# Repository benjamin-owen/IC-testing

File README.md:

# IC-testing
This repository contains a collection of ICs that I have tested.  Each folder from the root directory contains project files for the respective IC.  The file/folder structure follows my kicad-project-template template.

## Important version control information
This project uses submodules to keep libraries up-to-date.  The following commands must be used when cloning or to update the submodule with the latest commits:

To clone the repository:

```git clone --recurse-submodules <repo>```

To update the submodules:

```git submodule update --remote```

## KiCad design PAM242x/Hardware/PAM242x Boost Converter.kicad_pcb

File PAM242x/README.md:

Documentation and testing of the PAM242x boost converter IC

## Results

The PAM242x is a cheap and easy to use boost converter IC.  It works well with some voltage drop at extremely high currents, but that is to be expected.  The IC is very simple and can be used with LEDs to monitor its status.

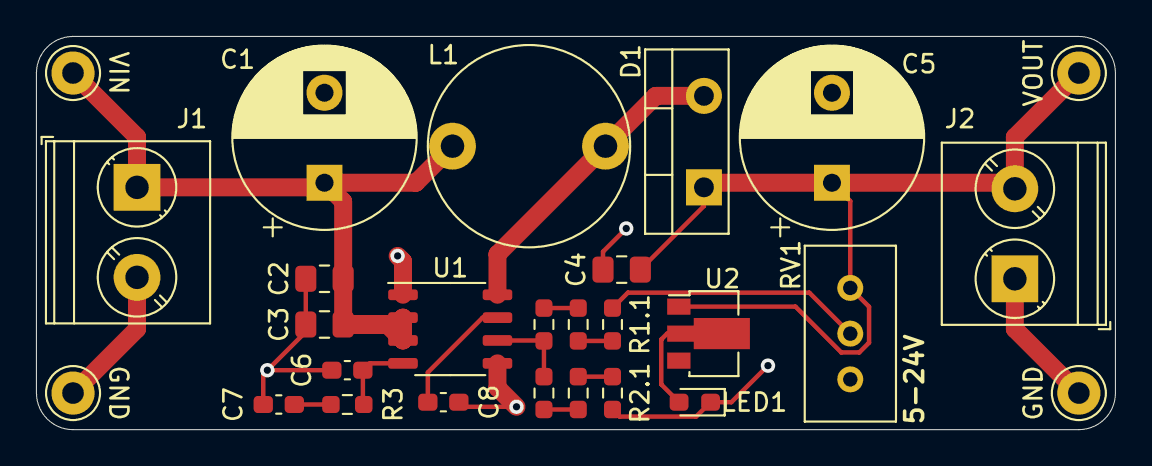
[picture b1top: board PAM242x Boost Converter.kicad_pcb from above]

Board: 2 copper layers, 59.9 x 21.8 mm, 27 parts (0 on the bottom side), 14 nets.

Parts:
C1, C5: 470uF; CP_Radial_D10.0mm_P5.00mm
C2, C4: 10uF; C_0805_2012Metric_Pad1.18x1.45mm_HandSolder
C3: 1uF; C_0805_2012Metric_Pad1.18x1.45mm_HandSolder
C6: 47pF; C_0603_1608Metric_Pad1.08x0.95mm_HandSolder
C7: 2.2nF; C_0603_1608Metric_Pad1.08x0.95mm_HandSolder
C8: 10nF; C_0603_1608Metric_Pad1.08x0.95mm_HandSolder
D1: D_Schottky; TO-220-2_Vertical
GND: Pin header; Pin_D1.0mm_L10.0mm_LooseFit
GND#2: Pin header; Pin_D1.0mm_L10.0mm_LooseFit
J1, J2: Screw terminal; TerminalBlock_Phoenix_PT-1,5-2-5.0-H_1x02_P5.00mm_Horizontal
L1: 6.8uH; L_Radial_D11.0mm_P8.50mm
LED1: GREEN; LED_0603_1608Metric_Pad1.05x0.95mm_HandSolder
R1.1: 560; R_0603_1608Metric_Pad0.98x0.95mm_HandSolder
R1.2: 9K1; R_0603_1608Metric_Pad0.98x0.95mm_HandSolder
R1.3: 10K; R_0603_1608Metric_Pad0.98x0.95mm_HandSolder
R2.1: 240; R_0603_1608Metric_Pad0.98x0.95mm_HandSolder
R2.2: 1K3; R_0603_1608Metric_Pad0.98x0.95mm_HandSolder
R2.3: 5K1; R_0603_1608Metric_Pad0.98x0.95mm_HandSolder
R3: 51K; R_0603_1608Metric_Pad0.98x0.95mm_HandSolder
RV1: 100K; Potentiometer_Bourns_3296W_Vertical
U1: PAM242x; SOP-8_3.9x4.9mm_P1.27mm
U2: CL2N8-G; SOT-89-3
VIN: Pin header; Pin_D1.0mm_L10.0mm_LooseFit
VOUT: Pin header; Pin_D1.0mm_L10.0mm_LooseFit

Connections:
GND: C1.2, C2.2, C3.2, C4.2, C5.2, C6.2, C7.2, C8.2, GND.1, GND#2.1, J1.2, J2.1, LED1.1, R2.3.2, U1.1, U1.5
unnamed: C6.1, R3.1, U1.4
unnamed: C7.1, R3.2
unnamed: C8.1, U1.7
unnamed: D1.2, L1.2, U1.8
unnamed: LED1.2, U2.2
unnamed: R1.1.1, R1.2.2
unnamed: R1.1.2, R2.1.1, U1.6
unnamed: R1.2.1, R1.3.2
unnamed: R1.3.1, RV1.2
unnamed: R2.1.2, R2.2.1
unnamed: R2.2.2, R2.3.1
VIN: C1.1, C2.1, C3.1, J1.1, L1.1, U1.2, U1.3, VIN.1
VOUT: C4.1, C5.1, D1.1, J2.2, RV1.1, U2.1, VOUT.1

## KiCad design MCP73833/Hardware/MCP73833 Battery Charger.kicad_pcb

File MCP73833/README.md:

Documentation and testing of the MCP73833 lithium ion battery charger IC

## Results

The MCP73833 was an effective battery charge IC.  However, the chip becomes VERY hot under load, so a heatsink or thermal vias are necessary for safe operation.

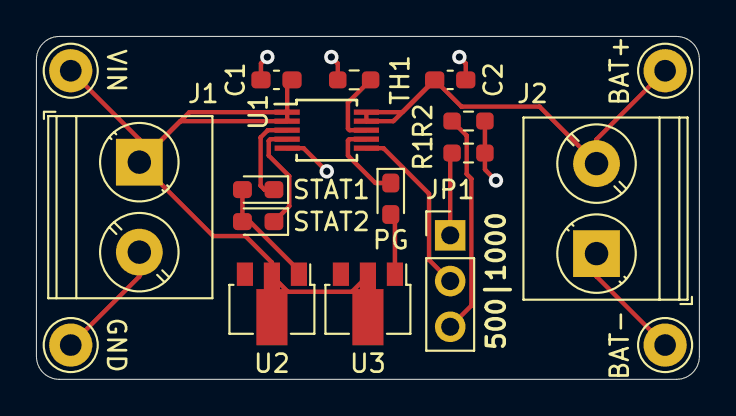
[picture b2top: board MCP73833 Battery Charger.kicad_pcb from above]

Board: 2 copper layers, 36.8 x 19.0 mm, 18 parts (0 on the bottom side), 12 nets.

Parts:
BAT+: Pin header; Pin_D1.0mm_L10.0mm_LooseFit
BAT-: Pin header; Pin_D1.0mm_L10.0mm_LooseFit
C1, C2: 1uF; C_0603_1608Metric_Pad1.08x0.95mm_HandSolder
GND: Pin header; Pin_D1.0mm_L10.0mm_LooseFit
J1, J2: Screw terminal; TerminalBlock_Phoenix_PT-1,5-2-5.0-H_1x02_P5.00mm_Horizontal
JP1: ISEL; PinHeader_1x03_P2.54mm_Vertical
PG: GREEN; LED_0603_1608Metric_Pad1.05x0.95mm_HandSolder
R1: 1K; R_0603_1608Metric_Pad0.98x0.95mm_HandSolder
R2: 2K; R_0603_1608Metric_Pad0.98x0.95mm_HandSolder
STAT1: RED; LED_0603_1608Metric_Pad1.05x0.95mm_HandSolder
STAT2: GREEN; LED_0603_1608Metric_Pad1.05x0.95mm_HandSolder
TH1: 10K; R_0603_1608Metric_Pad0.98x0.95mm_HandSolder
U1: MCP73833; MSOP-10_3x3mm_P0.5mm
U2, U3: CL2N8-G; SOT-89-3
VIN: Pin header; Pin_D1.0mm_L10.0mm_LooseFit

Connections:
GND: BAT-.1, C1.2, C2.2, GND.1, J1.2, J2.1, R1.2, R2.2, TH1.1, U1.5
unnamed: JP1.1, R1.1
unnamed: JP1.2, U1.6
unnamed: JP1.3, R2.1
unnamed: STAT1.1, U1.3
unnamed: STAT1.2, STAT2.2, U2.1
unnamed: STAT2.1, U1.4
unnamed: PG.1, U1.7
unnamed: PG.2, U3.1
unnamed: TH1.2, U1.8
VIN: C1.1, J1.1, U1.1, U1.2, U2.2, U3.2, VIN.1
VOUT: BAT+.1, C2.1, J2.2, U1.9, U1.10

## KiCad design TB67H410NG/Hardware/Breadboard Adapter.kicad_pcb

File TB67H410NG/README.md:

Documentation and testing of the TB67H410NG motor driver IC

## Results

The TB67H410NG was not effective for high current motor driver applications.  Even when using "large mode" for higher current draw, the voltage drop under load was so large that the motor could never reach maximum speed.  Additionally, the abnormal footprint made it difficult to test without a custom breadboard adapter.

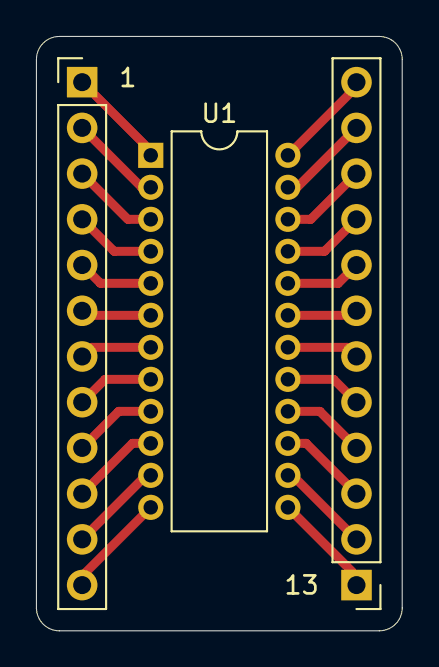
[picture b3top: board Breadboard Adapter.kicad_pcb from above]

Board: 2 copper layers, 20.3 x 33.0 mm, 3 parts (0 on the bottom side), 24 nets.

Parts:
1, 13: Pin header; PinHeader_1x12_P2.54mm_Vertical
U1: TB67H410NG; SDIP-24_W7.62mm

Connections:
unnamed: 1.1, U1.1
unnamed: 1.2, U1.2
unnamed: 1.3, U1.3
unnamed: 1.4, U1.4
unnamed: 1.5, U1.5
unnamed: 1.6, U1.6
unnamed: 1.7, U1.7
unnamed: 1.8, U1.8
unnamed: 1.9, U1.9
unnamed: 1.10, U1.10
unnamed: 1.11, U1.11
unnamed: 1.12, U1.12
unnamed: 13.1, U1.13
unnamed: 13.2, U1.14
unnamed: 13.3, U1.15
unnamed: 13.4, U1.16
unnamed: 13.5, U1.17
unnamed: 13.6, U1.18
unnamed: 13.7, U1.19
unnamed: 13.8, U1.20
unnamed: 13.9, U1.21
unnamed: 13.10, U1.22
unnamed: 13.11, U1.23
unnamed: 13.12, U1.24

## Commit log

2022-01-06 Move to correct folder
2022-01-06 Update submodules
2022-01-06 Add files from old repo
2022-01-06 Remove unused folders
2022-01-06 Ignore KiCAD backup files
2022-01-06 Add datasheets
2022-01-06 Add IC-specific README
2022-01-06 Add results
2022-01-06 Update schematic (unfinished)
2022-01-07 Add Arduino PWM code
2022-01-07 Add MCP73833 data
2022-01-07 Add PAM242x data
2022-03-20 Add IS and SR circuitry
